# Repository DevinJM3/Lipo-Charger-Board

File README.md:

# LiPo Charger & Protection Board with 5V Output

PLACEHOLDER FOR IMAGE

## Overview

This project is a custom-designed Lithium Polymer battery charging and protection circuit with a regulated 5V output. Perfect for powering your portable electronics projects, this board offers a complete power management solution in a compact form factor.

## Features

- **LiPo Battery Charging**: Safe charging circuit for single-cell LiPo batteries
- **Battery Protection**: Overcharge, over-discharge, and short-circuit protection
- **5V Regulated Output**: Clean, stable 5V output regardless of battery voltage
- **Compact Design**: Minimized footprint for easy integration into projects
- **Status Indicators**: LED indicators for charging/full charge
- **USB Input**: Standard USB-C connector for charging and power input

## Technical Specifications

- **Input Voltage**: 5V DC via USB
- **Battery**: Single-cell 3.7V Lithium Polymer
- **Charging Current**: 500mA (configurable)
- **Output Voltage**: 5V ±0.1V
- **Maximum Output Current**: 2A continuous
- **Protection Features**:
  - Overcharge cutoff: 4.2V
  - Over-discharge cutoff: 2.8V
  - Short-circuit protection

## PCB Details

- **Dimensions**: XX mm × XX mm
- **Layers**: 2-layer PCB
- **Designed with**: KiCad 9.0

## Getting Started

### Bill of Materials

| Designator |                Footprint                | Quantity |      Value      | LCSC Part # |
|------------|-----------------------------------------|----------|-----------------|-------------|
| C1, C2     |0603                                     |2         |10uF             |C19702       |
| C3         |0603                                     |1         |0.1uF            |C14663       |
| C4, C5     |0603                                     |2         |22uF             |C59461       |
| D1         |0603                                     |1         |RED              |C965799      |
| D2         |0603                                     |1         |GREEN            |C19171301    |
| D3         |D_SMA-SMB_Universal_Handsoldering        |1         |SS34             |C908680      |
| D4, D5     |D_SMA-SMB_Universal_Handsoldering        |2         |B340A            |C85098       |
| D6         |Nexperia_CFP3_SOD-123W                   |1         |5.1v             |C19077401    |
| J1         |JST_S2B-XH-A                             |1         |S2B-XH-A         |C157931      |
| J2         |Usb-C                                    |1         |USB_C_USB2.0_14P |C2988369     |
| L1         |WE-PD2_1054                              |1         |22uH             |C436465      |
| Q1, Q2     |SOT-23_Handsoldering                     |2         |SI2300A          |C347480      |
| R1, R5     |0603                                     |2         |2k               |C2907022     |
| R10        |0603                                     |1         |73.2k            |C2933257     |
| R11, R7    |0603                                     |2         |10k              |C98220       |
| R2, R3     |0603                                     |2         |1k               |C103198      |
| R4         |0603                                     |1         |100              |C3016239     |
| R6         |0603                                     |1         |0.4              |C5126047     |
| R8, R9     |0603                                     |2         |5.1k             |C3016319     |
| SW1        |SlideSwitch                              |1         |SK12D07VG4       |C393937      |
| U1         |SOIC-8                                   |1         |TP4056-42-ESOP8  |C725790      |
| U2         |SOT-23-6                                 |1         |MT3608           |C84817       |
| U3         |TSOT-23-6_HandSoldering                  |1         |FM2113           |C2832124     |

## Usage

1. Connect a LiPo battery to the BAT+ and BAT- terminals
2. Power the board via the USB connector
3. Connect your load to the 5V and GND output terminals
4. The charging indicator LED will illuminate red during charging and turn green when complete

## License

This project is released under the [MIT License](LICENSE).

## Contributing

Contributions to improve the design are welcome! Please feel free to submit issues or pull requests.

## Contact

If you have any questions or suggestions about this project, please open an issue on GitHub or contact me at Devin.Marx3@gmail.com.

---

*This is my first KiCad project! I appreciate any feedback or suggestions for improvement.*

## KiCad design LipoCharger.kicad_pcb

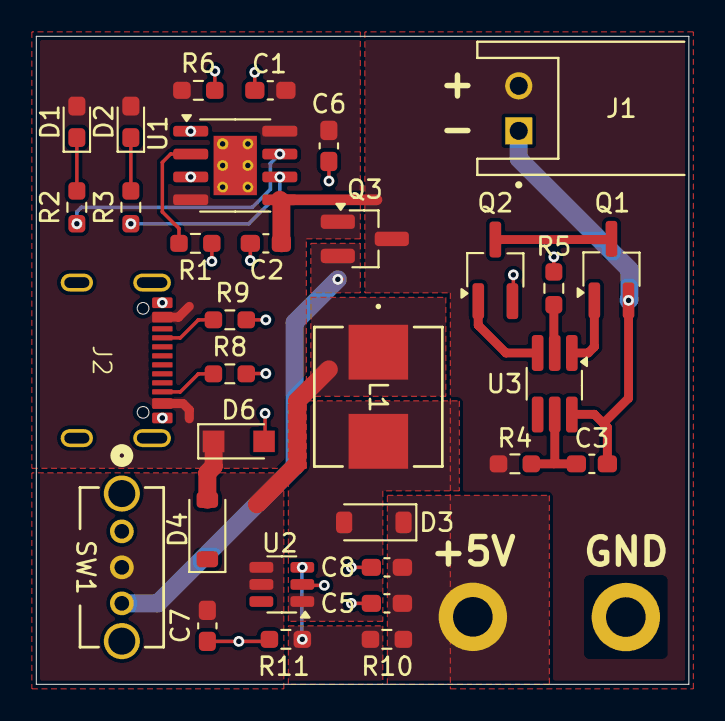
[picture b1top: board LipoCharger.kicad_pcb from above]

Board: 4 copper layers, 36.2 x 36.0 mm, 35 parts (1 on the bottom side), 21 nets.

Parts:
C1, C2, C5, C8: 22uF; C_0603_1608Metric_Pad1.08x0.95mm_HandSolder
C3, C6, C7: 100nF; C_0603_1608Metric_Pad1.08x0.95mm_HandSolder
D1: RED; LED_0603_1608Metric_Pad1.05x0.95mm_HandSolder
D2: GREEN; LED_0603_1608Metric_Pad1.05x0.95mm_HandSolder
D3, D4: MBR230LSFT1G; D_SOD-123
D6: 5.1v; Nexperia_CFP3_SOD-123W
Devin M.: LOGO; PCB Logo (12.5x17)
GND_OUT1: MountingHole; MountingHole_2.2mm_M2_DIN965_Pad
J1: S2B-XH-A; JST_S2B-XH-A
J2: USB_C_Receptacle_USB2.0_14P; Usb-C
L1: 10uH; HY0630-100M-M
PWR_OUT1: MountingHole; MountingHole_2.2mm_M2_DIN965_Pad
Q1, Q2: SI2300A; TSOT-23_HandSoldering
Q3: HL 2305A; SOT-23_Handsoldering
R1, R5: 2k; R_0603_1608Metric_Pad0.98x0.95mm_HandSolder
R2, R3: 1k; R_0603_1608Metric_Pad0.98x0.95mm_HandSolder
R4: 100; R_0603_1608Metric_Pad0.98x0.95mm_HandSolder
R6: 10k; R_0603_1608Metric_Pad0.98x0.95mm_HandSolder
R8, R9: 5.1k; R_0603_1608Metric_Pad0.98x0.95mm_HandSolder
R10: 82k; R_0603_1608Metric_Pad0.98x0.95mm_HandSolder
R11: 11k; R_0603_1608Metric_Pad0.98x0.95mm_HandSolder
SW1: SK12D07VG4; SK12D07VG4 - (SlideSwitch)
U1: TP4056-42-ESOP8; SOIC-8-1EP_3.9x4.9mm_P1.27mm_EP2.41x3.3mm_ThermalVias
U2: MT3608; SOT-23-6
U3: FM2113; TSOT-23-6_HandSoldering

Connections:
+BATT: C2.1, J1.2, Q3.3 (D), R4.1, U1.5 (BAT)
-BATT: C3.2, J1.1, Q1.2 (S), U3.6 (VSS)
/SW: D3.2 (A), L1.2, U2.1 (SW)
BOOST_IN: C7.1, L1.1, SW1.2, U2.4 (EN), U2.5 (IN)
GND: C1.2, C2.2, C5.2, C6.2, C7.2, C8.2, D6.2 (A), GND_OUT1.1, J2.A1 (GND), Q2.2 (S), R1.2, R5.2, R6.1, R8.2, R9.2, R11.2, SW1.1, U1.1 (TEMP), U1.3 (GND), U1.9 (EPAD), U2.2 (GND)
unnamed: D1.1 (K), R2.1
unnamed: D2.1 (K), R3.1
unnamed: C5.1, C8.1, D3.1 (K), PWR_OUT1.1, R10.1
unnamed: D4.1 (K), Q3.2 (S), SW1.3
unnamed: J2.A5 (CC1), R9.1
unnamed: J2.B5 (CC2), R8.1
unnamed: Q1.3 (D), Q2.3 (D)
unnamed: Q1.1 (G), U3.1 (OD)
unnamed: Q2.1 (G), U3.3 (OC)
unnamed: R1.1, U1.2 (PROG)
unnamed: R2.2, U1.7 (~CHRG)
unnamed: R3.2, U1.6 (~STDBY)
unnamed: R10.2, R11.1, U2.3 (FB)
unnamed: R5.1, U3.2 (CS)
unnamed: C3.1, R4.2, U3.5 (VDD)
VBUS: C1.1, C6.1, D1.2 (A), D2.2 (A), D4.2 (A), D6.1 (K), J2.A4 (VBUS), Q3.1 (G), R6.2, U1.4 (V_{CC}), U1.8 (CE)

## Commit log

2025-05-06 Inital Commit
2025-05-07 Added the DW01 Battery Protection IC and started adding the USB-C port
2025-05-07 Replaced the DW01 with a FM2113
    The DW01 was not suited for a LIPO battery, the under voltage threshold was too low, so it was replaced with the FM2113 which has a much higher threshold
2025-05-08 Updated usb-c connector, added the 5v switcher, and started to find specific components for the swithcher
2025-05-08 Cleaned up schematic and added a slide switch
    * Added a slide switch for enabling the 5v Switcher
    * Added the USB protection and part numbers
    * Consolidated all of the symbols into the Symbols folder (instead of the _Library.pretty folder)
2025-05-08 Fixed ERC errors
2025-05-08 Started laying out the board
    Charging circuit should be finalized
2025-05-08 updated part numbers to add stock, added part numbers to each part
2025-05-09 Finished Layout and routing, just need to add mounting holes
2025-05-09 Updated ERC Exclusions
2025-05-09 Updated DRC
2025-05-09 Update KiCad.yml
    updated kicad actions version
2025-05-09 Made some small changes and added my "Logo"
2025-05-09 Updated kicad version and fixed drc
2025-05-12 Updated to add power pathing for usb and charging ic
2025-05-13 added the updated inductor and update the model for the PMOS mosfet (Should update the NMOS)
2025-05-15 Reoriented the PCB for the updated schematic layout
2025-05-15 Routed some traces (Almost finished routing)
2025-05-16 fixed nmos footprints
2025-05-23 Fixed most of the DRC
2025-05-23 Moved vias outside off of the pads
2025-05-30 Updated LCSC Part Numbers
2025-05-30 Fixed part number on BOM
2025-07-03 Fixed issue that would allow power to flow even thought the power switch is turned off
2025-07-03 updated gitignore
